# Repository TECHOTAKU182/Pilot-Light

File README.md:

# Pilot Light

一个紧凑型 USB RGB 状态信号灯的开源硬件项目。当前设计版本为 **SL25 Rev B**：通过 CH552G 控制一颗位于正面中心的 WS2812B-V5，使用单个直径 24 mm 的扩散灯窗显示红、黄、绿等状态。

> 本仓库包含可编辑的 PCB、外壳和制造文件，但尚未完成实物打样、光学测试、USB 功能验证或电脑状态采集软件。制造与使用前请自行复核并完成测试。

## 当前设计

| 项目 | SL25 Rev B 规格 |
| --- | --- |
| PCB | 25 x 25 mm、双层、1.6 mm 厚 |
| 光源 | 正面中心 WS2812B-V5 RGB LED |
| 控制器 | CH552G，LED 数据输出为 P1.5 |
| 接口 | 背面 USB-C，USB 2.0 全速原型电路 |
| 外壳 | 30 x 30 x 40 mm |
| 灯窗 | 正面中心直径 24 mm，PET 扩散膜与透明 PC 保护片 |
| 遮光檐 | 顶部前伸 15 mm，两侧连续收短 |

该设计的光学结构从外到内依次为：黑色遮光帽、透明 PC 保护片、PET 扩散膜、泡棉压圈、白色混光腔与中心 RGB LED。白色混光腔是获得较均匀光效的必要零件，不能以黑色打印件替代。

## 仓库结构

| 路径 | 内容 |
| --- | --- |
| [`hardware/sl25_rev_b/`](hardware/sl25_rev_b/) | 当前 Rev B KiCad 工程、BOM、Gerber、贴片坐标、3D 模型与检查报告 |
| [`enclosure/sl25_traffic_rev_b/`](enclosure/sl25_traffic_rev_b/) | 当前 Rev B FreeCAD 工程、STEP、STL、光学片裁切模板与装配说明 |
| [`firmware/ch552_ws2812_demo/`](firmware/ch552_ws2812_demo/) | 用于焊后点灯检查的最小 CH552G 示例程序 |
| [`hardware/reference/`](hardware/reference/) | 器件数据手册和参考图纸 |
| [`SL25-RevB-complete.zip`](SL25-RevB-complete.zip) | Rev B 完整交付包 |
| [`hardware/SL25-RevB-gerbers.zip`](hardware/SL25-RevB-gerbers.zip) | Rev B PCB 制板文件包 |
| [`enclosure/SL25-Traffic-STL-RevB.zip`](enclosure/SL25-Traffic-STL-RevB.zip) | Rev B 3D 打印和膜片裁切文件包 |

`hardware/sl25/` 与 `enclosure/sl25_traffic/` 为历史 Rev A 文件，仅供参考。Rev A 和 Rev B 的 LED、元件安装面、外壳及控制方式不兼容，不能混用。

## 制造与装配

1. 使用 `hardware/SL25-RevB-gerbers.zip` 下单 PCB；建议规格为 FR-4、2 层、1.6 mm、1 oz 铜。
2. 根据 [`hardware/sl25_rev_b/BOM.csv`](hardware/sl25_rev_b/BOM.csv) 和 [`MATERIALS.md`](hardware/sl25_rev_b/MATERIALS.md) 采购并装配；所有元件和 USB-C 均在 PCB 背面，只有 WS2812B-V5 位于正面。
3. 打印 Rev B 的四个外壳件。前壳和遮光帽使用黑色材料，混光腔必须使用不透光白色材料；建议 PETG、0.4 mm 喷嘴、0.16-0.20 mm 层高。
4. 按 `cut_templates/` 中 1:1 SVG 裁切直径 26 mm 的透明 PC 保护片、PET 扩散膜和泡棉环；先测量模板中的 10 x 10 mm 校准框。
5. 参考 [外壳装配说明](enclosure/sl25_traffic_rev_b/README.md) 完成装配。需要两颗 M2 x 12、头径不超过 4.0 mm 的 90 度沉头螺丝。
6. 使用 [`firmware/ch552_ws2812_demo/`](firmware/ch552_ws2812_demo/) 的台架程序确认红、绿、蓝、黄依次点亮，再进行完整功能开发。

完整尺寸、材料规格、打印方向、光学叠层和拆装步骤见 [外壳 README](enclosure/sl25_traffic_rev_b/README.md)。电路、USB/LED 引脚、制造规则和检验结果见 [PCB README](hardware/sl25_rev_b/README.md)。

## 开发与重建

- PCB 使用 KiCad 10。更新设计时，先保留手工修改，再依次运行 `hardware/generate_rev_b.py`、`hardware/route_rev_b.py` 和 `hardware/finish_board.py`；这些生成流程会覆盖已有输出。
- 外壳使用 FreeCAD。修改 `enclosure/sl25_traffic_rev_b/parameters.json` 后，依次运行 `build.py`、`finish_cad.py`、`render.py` 和 `cut_templates.py`。
- 固件使用 SDCC，并需要 WCH CH55X EVT 提供的启动文件。示例程序只用于点灯检查，正式固件应加入 USB 枚举、主机命令超时关灯、USB 挂起关灯和看门狗。

## 验证状态与限制

仓库中的 ERC、DRC、制造文件、模型资产和几何干涉检查已通过，但以下事项尚待实物确认：

- USB 电气性能、枚举和 USB-C 兼容性
- LED 的 WS2812 时序、功耗、温升和各颜色亮度
- 扩散膜下的均匀度、色斑和黄色配比
- 3D 打印公差、膜材厚度、螺丝配合和机械耐久

本项目不是通过认证的交通信号灯，也不应在安全关键或监管用途部署。

## 许可证

尚未指定许可证。在许可证补充前，请先联系仓库所有者确认使用、修改和分发权限。

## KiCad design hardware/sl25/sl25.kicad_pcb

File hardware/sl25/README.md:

# SL25 状态灯 PCB，Rev A

这是一块面向个人原型的 25 × 25 mm 双层 USB 状态灯 PCB，可用于正面宽、高均不超过 30 mm 的外壳。当前完成硬件设计和软件规则检查，尚未制作、焊接或实测。固件、Windows 状态采集程序和外壳工程不包含在本次交付中。

## 打开工程

使用 KiCad 10 打开 `sl25.kicad_pro`，分别进入原理图和 PCB 编辑器。符号、封装和所用 STEP 模型均随工程提供。KiCad 三维查看器可查看装配效果。

| 文件 | 内容 |
| --- | --- |
| `sl25.kicad_sch` | 单页原理图 |
| `sl25.kicad_pcb` | 已布线、铺铜的 PCB |
| `BOM.csv` | 逐项材料表，含准确型号与安装面 |
| `MATERIALS.md` | 中文采购及装配说明 |
| `checks/erc.rpt`、`checks/drc.rpt` | 最终规则检查报告 |
| `fabrication/` | Gerber、独立 PTH/NPTH 钻孔、贴装坐标 |
| `mechanical/sl25.step` | 含元件的装配 STEP，供外壳设计参考 |
| `mechanical/interface.json` | 板框、安装孔和接口位置 |
| `preview/` | 原理图 SVG 及 PCB 正反面、立体预览 |

本文件夹中的材料表替代之前讨论的 Pico 开发板和洞洞板采购方案。USB-C 插座必须匹配指定封装，不能仅凭“16 脚 Type-C”购买替代件。

## 电路

- USB-C 仅使用 USB 2.0 数据与 5 V 供电，CC1、CC2 各自用 5.1 kΩ 电阻接地。没有 USB PD 升压、电池或外部电源接口。
- CH552G 使用 SOP-16 窄体封装、内部振荡器和内部 USB 上拉。VCC 接 USB 5 V；V33 仅接 100 nF 去耦，不能短接到 5 V。
- USBLC6-2SC6 在背面保护 D+、D-；C4 是其电源去耦。插座金属壳直接接 GND，壳体焊脚直接接地铜皮。
- 单颗共阴 RGB 灯的每个阳极分别串 1 kΩ，限流后由 MCU GPIO 驱动。以 5.25 V 和 1% 电阻下限估算，即使忽略 LED 压降，单路电流也不超过 5.31 mA。
- JP1 平时保持断开；通过 10 kΩ 将 D+ 临时拉到 5 V，在上电时请求兼容工厂 USB ISP 的下载模式。购买带工厂 USB ISP 的 CH552G。TP3–TP6 保留专用编程器信号，不能当作通用 SPI 外设接口。
- R7 将高有效 RESET 下拉到 GND。固件仍应采用上电复位和看门狗。

| 功能 | CH552G 物理脚 | GPIO | 备注 |
| --- | --- | --- | --- |
| 红灯 | 3 | P1.5 | PWM1；高电平亮 |
| 绿灯 | 11 | P3.4 | PWM2；高电平亮 |
| 蓝灯 | 9 | P1.1 | 普通 GPIO，默认关闭 |
| USB D+ | 12 | P3.6 | USB 功能 |
| USB D- | 13 | P3.7 | USB 功能 |
| RESET | 6 | RST | 高有效 |

红加绿形成黄色。PWM 占空比需在样板和最终灯罩上调整，不能保证两路相同占空比就得到视觉上均匀的黄色。

## 固件与电脑端约定

建议后续固件使用 USB HID 接收颜色、亮度和灯效命令，Windows 程序通过 HID 库发送，无需增加 USB 转串口芯片。未配置、USB 挂起和主机命令超时应关闭 LED；初始化时先将三路输出置低，再使能输出，红绿用硬件 PWM，蓝色默认不用。

USB VID/PID 和描述符在固件阶段确定，不能未经授权用于发布产品。USB 功耗描述和挂起电流必须与实测匹配。当前电路未验证 USB 枚举、信号质量、EMC 或 ESD 性能；放置保护器件不等于通过系统级认证。

Windows 桌面版 Codex 的实时状态来源仍需单独验证。PCB 本身只接收灯光命令，不会自动读取 Codex。

## 制板与机械

建议首批 5 块样板：双层 FR-4、1.6 mm、1 oz 铜、绿色阻焊、白色丝印；优先选择平整表面处理，USB-C 手焊可选沉金。没有阻抗控制声明。

布线宽度 0.20 mm，设计最小铜间距 0.15 mm；过孔 0.60 / 0.30 mm。安装孔 2.20 mm，LED 孔 0.90 mm；PTH 和 NPTH 分开导出。USB4105 厂家推荐焊盘到定位孔的最近距离约 0.194 mm，本项目孔到铜间距规则设为 0.18 mm；下单时需要工厂支持这一要求。没有通过忽略 DRC 错误来放行设计。

板框圆角半径 1 mm。以 PCB 左上角为平面坐标原点，X 向右、Y 向下：

| 项目 | 位置或尺寸，mm |
| --- | --- |
| PCB 外形 | 25 × 25 × 1.6 |
| H1、H2 安装孔 | (2.7, 2.7)、(22.3, 2.7)，孔径 2.2 |
| D1 光学中心 | (12.5, 3.5)，靠近板上边，不在板中心 |
| USB 插座封装原点 | (12.5, 21.15)，插拔方向朝下边 |
| USB 插座本体 | 厂家宽 8.94、长 7.35、高 3.31 |
| LED 引脚孔 | X=9.2615 / 11.4205 / 13.5795 / 15.7385；Y=3.5 |

建议外壳先按 30 × 30 × 25 mm 预留，厚度尚未与用户锁定。壁厚与装配间隙需在外壳建模时分配，底面需留出 U2、C4 和焊点空间。两个 M2 安装柱配合底部承托或导轨固定 PCB，避免 USB 插拔力只作用在焊脚上。

LED 需用工具夹住靠近封装的一段引脚，再将外侧引脚整形成 2.159 mm 间距，封装底面离板约 3 mm，不要紧贴树脂根部弯折。灯珠顶面及焊接公差在外壳内至少按板上方 12.5 mm 预留，再留混光距离。STEP 中 LED 为通用 KiCad 模型，蓝色外观只是模型材质；实际指定灯珠为透明 RGB。该模型不能替代实物高度和透光测试。

STEP 使用 PCB 左上角 `(100,100)` 作为导出原点；CAD 的 Y 轴可能与上述 PCB 屏幕坐标相反，导入后以安装孔和 USB 方向识别朝向。

## 验证状态

2026-09-05 使用 KiCad 10.0.6：ERC 为 0 错误、0 警告；DRC 为 0 违规、0 未连接、0 原理图一致性问题。检查了厂家引脚图、封装尺寸图和正反面三维预览。

这些是设计文件检查，不能替代打样验证。未执行固件烧录、供电测量、USB 插头正反插、亮度混色、热稳定、休眠恢复及外壳装配测试。USB 数据布线为短距离原型布线，未做阻抗提取或信号完整性仿真。

## 设计依据与库许可

- WCH CH552/CH551 数据手册 V1G，第 3–4、19、31–33、70 页；`../reference/CH552.pdf` 为 WCH 原文的 Adafruit 镜像。厂家入口：https://www.wch-ic.com/downloads/CH552DS1_PDF.html
- Kingbright WP154A4SUREQBFZGC，第 1–2 页：https://www.kingbrightusa.com/images/catalog/spec/WP154A4SUREQBFZGC.pdf
- GCT USB4105 厂家图纸：https://gct.co/files/drawings/usb4105.pdf
- ST USBLC6-2SC6：https://www.st.com/resource/en/datasheet/usblc6-2.pdf
- ch55xduino 工程及 USB ISP 上电方式：https://github.com/DeqingSun/ch55xduino
- 随附封装、STEP 模型来自 KiCad 官方库，适用 KiCad 库许可及其例外：https://www.kicad.org/libraries/license/ 。通用芯片模型只表示封装，并不代表芯片品牌或实物标识。

## 重新生成

已交付文件可以直接在 KiCad 中编辑。只有需要重新生成初始设计时才执行以下脚本；重新生成会覆盖手工改板结果，先保留自己的修改。

在项目根目录运行 KiCad 自带 Python：依次执行 `hardware/generate_board.py`、`hardware/route_board.py`、`hardware/finish_board.py`。默认工具路径是本机的 `E:/Kicard`，其他电脑可调整 `KICAD_FOOTPRINT_DIR`、`KICAD_3DMODEL_DIR`。渲染需要 KiCad 用户缓存目录可写，否则可能只显示裸板。

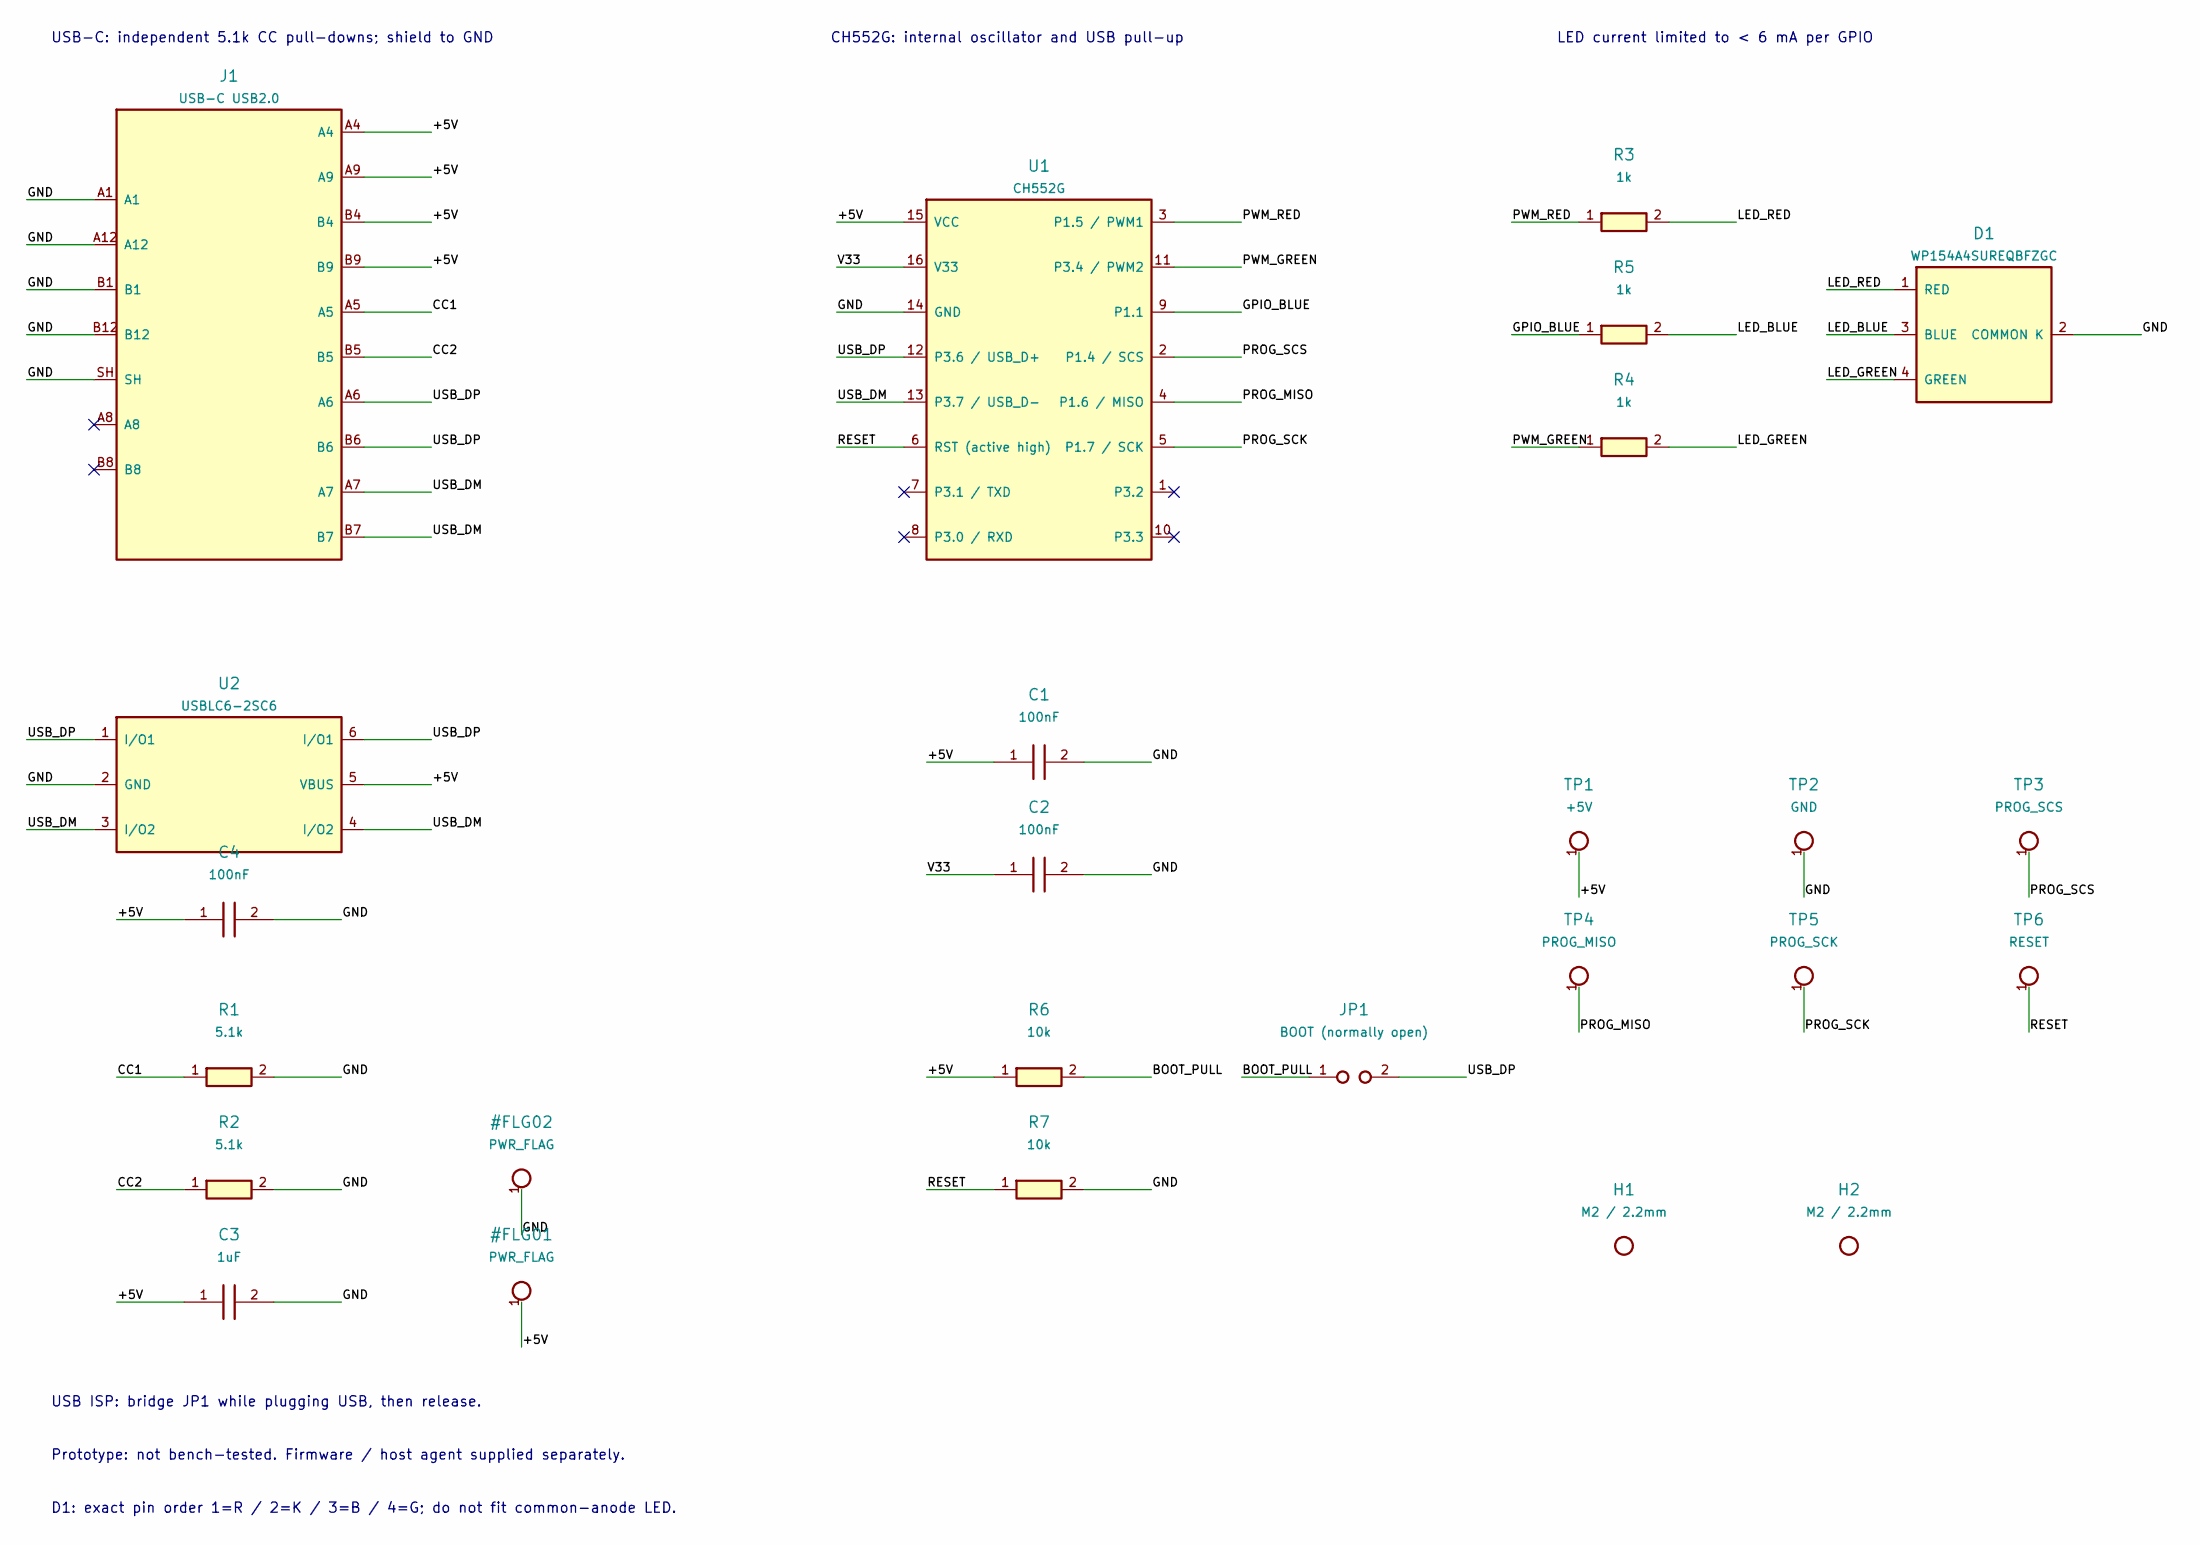
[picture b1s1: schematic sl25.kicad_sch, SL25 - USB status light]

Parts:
C1, C2, C4: 100nF; C_0805_2012Metric
C3: 1uF; C_0805_2012Metric
D1: WP154A4SUREQBFZGC; LED_D5.0mm-4_RGB_Wide_Pins
H1, H2: M2 / 2.2mm; MountingHole_2.2mm_M2
J1: USB-C USB2.0; USB_C_Receptacle_GCT_USB4105-xx-A_16P_TopMnt_Horizontal
JP1: BOOT (normally open); SolderJumper-2_P1.3mm_Open_RoundedPad1.0x1.5mm
R1, R2: 5.1k; R_0805_2012Metric
R3, R4, R5: 1k; R_0805_2012Metric
R6, R7: 10k; R_0805_2012Metric
TP1: +5V; TestPoint_Pad_D1.0mm
TP2: GND; TestPoint_Pad_D1.0mm
TP3: PROG_SCS; TestPoint_Pad_D1.0mm
TP4: PROG_MISO; TestPoint_Pad_D1.0mm
TP5: PROG_SCK; TestPoint_Pad_D1.0mm
TP6: RESET; TestPoint_Pad_D1.0mm
U1: CH552G; SOIC-16_3.9x9.9mm_P1.27mm
U2: USBLC6-2SC6; SOT-23-6

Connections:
/+5V: C1.1, C3.1, C4.1, J1.A4, J1.A9, J1.B4, J1.B9, R6.1, TP1.1, U1.15 (VCC), U2.5 (VBUS)
/BOOT_PULL: JP1.1, R6.2
/CC1: J1.A5, R1.1
/CC2: J1.B5, R2.1
/GND: C1.2, C2.2, C3.2, C4.2, D1.2 (COMMON K), J1.A1, J1.A12, J1.B1, J1.B12, J1.SH, R1.2, R2.2, R7.2, TP2.1, U1.14 (GND), U2.2 (GND)
/GPIO_BLUE: R5.1, U1.9 (P1.1)
/LED_BLUE: D1.3 (BLUE), R5.2
/LED_GREEN: D1.4 (GREEN), R4.2
/LED_RED: D1.1 (RED), R3.2
/PROG_MISO: TP4.1, U1.4 (P1.6 / MISO)
/PROG_SCK: TP5.1, U1.5 (P1.7 / SCK)
/PROG_SCS: TP3.1, U1.2 (P1.4 / SCS)
/PWM_GREEN: R4.1, U1.11 (P3.4 / PWM2)
/PWM_RED: R3.1, U1.3 (P1.5 / PWM1)
/RESET: R7.1, TP6.1, U1.6 (RST (active high))
/USB_DM: J1.A7, J1.B7, U1.13 (P3.7 / USB_D-), U2.3 (I/O2), U2.4 (I/O2)
/USB_DP: J1.A6, J1.B6, JP1.2, U1.12 (P3.6 / USB_D+), U2.1 (I/O1), U2.6 (I/O1)
/V33: C2.1, U1.16 (V33)

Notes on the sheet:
USB-C: independent 5.1k CC pull-downs; shield to GND
CH552G: internal oscillator and USB pull-up
LED current limited to < 6 mA per GPIO
USB ISP: bridge JP1 while plugging USB, then release.
Prototype: not bench-tested. Firmware / host agent supplied separately.
D1: exact pin order 1=R / 2=K / 3=B / 4=G; do not fit common-anode LED.

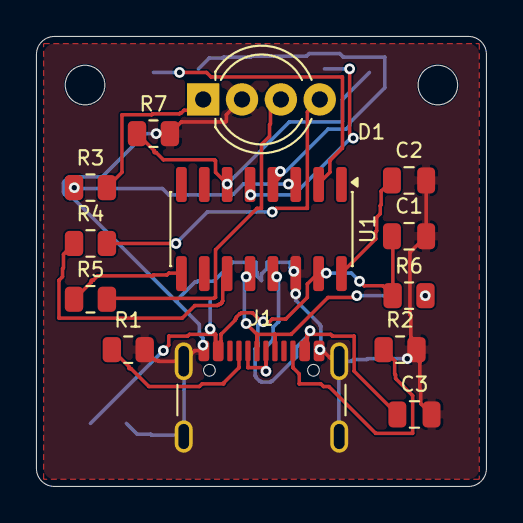
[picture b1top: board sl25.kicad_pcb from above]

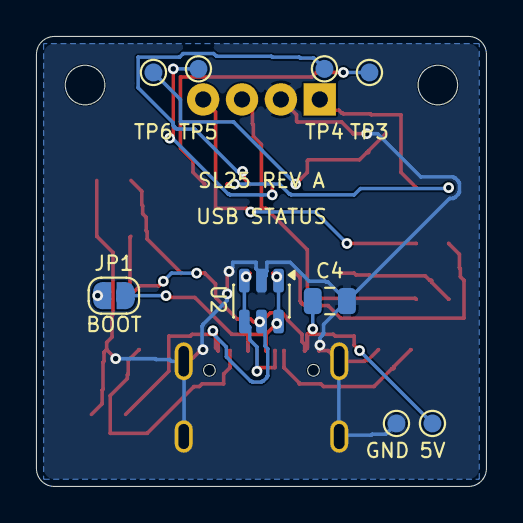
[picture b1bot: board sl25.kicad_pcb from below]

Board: 2 copper layers, 25.0 x 25.0 mm, 24 parts (9 on the bottom side), 18 nets.

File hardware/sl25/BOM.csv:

Reference,Value,MPN_or_specification,Footprint,Side,Quantity,Notes
J1,USB-C USB2.0,GCT USB4105-GF-A,Connector_USB:USB_C_Receptacle_GCT_USB4105-xx-A_16P_TopMnt_Horizontal,Top,1,Exact footprint required; USB-C socket is not interchangeable by appearance.
U1,CH552G,CH552G,Package_SO:SOIC-16_3.9x9.9mm_P1.27mm,Top,1,SOP16 150mil. Buy with factory USB ISP bootloader; do not substitute CH552T/E/P.
U2,USBLC6-2SC6,USBLC6-2SC6,Package_TO_SOT_SMD:SOT-23-6,Bottom,1,Bottom side; pins 1/6 and 3/4 are internally connected line pairs.
D1,WP154A4SUREQBFZGC,WP154A4SUREQBFZGC,LED_THT:LED_D5.0mm-4_RGB_Wide_Pins,Top,1,"Form 1.27mm native leads to 2.159mm PCB pitch with 3mm standoff. 1=R, 2=common K, 3=B, 4=G. Clear lens needs diffuser."
R1,5.1k,0805 5.1k 1% >=0.125W,Resistor_SMD:R_0805_2012Metric,Top,1,
R2,5.1k,0805 5.1k 1% >=0.125W,Resistor_SMD:R_0805_2012Metric,Top,1,
R3,1k,0805 1k 1% >=0.125W,Resistor_SMD:R_0805_2012Metric,Top,1,
R4,1k,0805 1k 1% >=0.125W,Resistor_SMD:R_0805_2012Metric,Top,1,
R5,1k,0805 1k 1% >=0.125W,Resistor_SMD:R_0805_2012Metric,Top,1,
R6,10k,0805 10k 1% >=0.125W,Resistor_SMD:R_0805_2012Metric,Top,1,
R7,10k,0805 10k 1% >=0.125W,Resistor_SMD:R_0805_2012Metric,Top,1,
C1,100nF,0805 100nF X7R 16V,Capacitor_SMD:C_0805_2012Metric,Top,1,
C2,100nF,0805 100nF X7R 16V,Capacitor_SMD:C_0805_2012Metric,Top,1,
C3,1uF,0805 1uF X7R 16V,Capacitor_SMD:C_0805_2012Metric,Top,1,
C4,100nF,0805 100nF X7R 16V,Capacitor_SMD:C_0805_2012Metric,Bottom,1,
JP1,BOOT (normally open),PCB touch pads,Jumper:SolderJumper-2_P1.3mm_Open_RoundedPad1.0x1.5mm,Bottom,1,Momentarily bridge during USB insertion; release after ISP enumeration. Do not solder closed.
TP1,+5V,PCB test pad,TestPoint:TestPoint_Pad_D1.0mm,Bottom,1,Programmer pads use 5V signaling; disconnect USB before external power.
TP2,GND,PCB test pad,TestPoint:TestPoint_Pad_D1.0mm,Bottom,1,Programmer pads use 5V signaling; disconnect USB before external power.
TP3,PROG_SCS,PCB test pad,TestPoint:TestPoint_Pad_D1.0mm,Bottom,1,Programmer pads use 5V signaling; disconnect USB before external power.
TP4,PROG_MISO,PCB test pad,TestPoint:TestPoint_Pad_D1.0mm,Bottom,1,Programmer pads use 5V signaling; disconnect USB before external power.
TP5,PROG_SCK,PCB test pad,TestPoint:TestPoint_Pad_D1.0mm,Bottom,1,Programmer pads use 5V signaling; disconnect USB before external power.
TP6,RESET,PCB test pad,TestPoint:TestPoint_Pad_D1.0mm,Bottom,1,Programmer pads use 5V signaling; disconnect USB before external power.
H1,M2 / 2.2mm,M2 mounting hole,MountingHole:MountingHole_2.2mm_M2,Top,1,
H2,M2 / 2.2mm,M2 mounting hole,MountingHole:MountingHole_2.2mm_M2,Top,1,

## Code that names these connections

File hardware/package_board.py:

"""Check critical hardware invariants and package the already-verified design."""
from pathlib import Path
import hashlib
import json
import math
import zipfile
import pcbnew as pcb

ROOT=Path(__file__).resolve().parent
DESIGN=ROOT/"sl25"
b=pcb.LoadBoard(str(DESIGN/"sl25.kicad_pcb"))
fps={f.GetReference():f for f in b.GetFootprints()}


def net(ref,pin):
    values={p.GetNetname().lstrip('/') for p in fps[ref].Pads() if p.GetNumber()==str(pin)}
    assert len(values)==1,(ref,pin,values)
    return values.pop()


# Pin assignments below are the externally reviewed datasheet expectations.
for pin,expected in {3:"PWM_RED",11:"PWM_GREEN",9:"GPIO_BLUE",12:"USB_DP",13:"USB_DM",14:"GND",15:"+5V",16:"V33"}.items():
    assert net("U1",pin)==expected
for pin,expected in {1:"LED_RED",2:"GND",3:"LED_BLUE",4:"LED_GREEN"}.items():
    assert net("D1",pin)==expected
for pin,expected in {"A6":"USB_DP","B6":"USB_DP","A7":"USB_DM","B7":"USB_DM","A5":"CC1","B5":"CC2","SH":"GND"}.items():
    assert net("J1",pin)==expected
assert net("R1",1)=="CC1" and net("R2",1)=="CC2"
assert net("R1",2)==net("R2",2)=="GND"
assert net("C2",1)=="V33" and net("C2",2)=="GND"
assert net("R6",1)=="+5V" and net("R6",2)==net("JP1",1)=="BOOT_PULL"
assert net("JP1",2)=="USB_DP"
for r in ["R3","R4","R5"]:assert fps[r].GetValue()=="1k"
assert b.GetCopperLayerCount()==2
assert abs(pcb.ToMM(b.GetDesignSettings().GetBoardThickness())-1.6)<.001
for ref,expected in [("H1",(102.7,102.7)),("H2",(122.3,102.7))]:
    assert math.dist(tuple(pcb.ToMM(fps[ref].GetPosition())),expected)<.001
    assert abs(pcb.ToMM(next(iter(fps[ref].Pads())).GetDrillSize().x)-2.2)<.001
for fp in b.GetFootprints():
    for m in fp.Models():
        assert m.m_Filename.startswith("${KIPRJMOD}/models/")
        assert (DESIGN/m.m_Filename.replace("${KIPRJMOD}/","")).is_file()
report=(DESIGN/"checks/drc.rpt").read_text(encoding="utf-8")
for text in ["Found 0 DRC violations","Found 0 unconnected pads","Found 0 Footprint errors"]:assert text in report
erc=(DESIGN/"checks/erc.rpt").read_text(encoding="utf-8")
assert "Errors 0" in erc and "Warnings 0" in erc
step=(DESIGN/"mechanical/sl25.step").read_text(encoding="utf-8")
for expected in ["SOIC-16_3.9x9.9mm_P1.27mm","LED_D5.0mm-4_RGB_Wide_Pins","USB_C_Receptacle_GCT_USB4105","SOT-23-6"]:assert expected in step
for file in ["sl25-PTH.drl","sl25-NPTH.drl","sl25-F_Cu.gtl","sl25-B_Cu.gbl","sl25-Edge_Cuts.gm1"]:
    assert (DESIGN/"fabrication"/file).stat().st_size>100

result={"tool":"KiCad 10.0.6","revision":"A","status":"design_checks_passed_not_bench_tested",
        "footprints":len(fps),"copper_layers":2,"board_mm":[25,25,1.6],
        "erc_errors":0,"erc_warnings":0,"drc_violations":0,"unconnected_pads":0,"schematic_parity_issues":0,
        "critical_pinmap_checks":"passed","local_model_paths":"passed","step_contains_component_models":"passed",
        "physical_validation":"not performed"}
(DESIGN/"checks/verification.json").write_text(json.dumps(result,indent=2),encoding="utf-8")

files=[p for p in DESIGN.rglob("*") if p.is_file() and not p.name.endswith((".lck",".kicad_prl"))]
hashes={str(p.relative_to(DESIGN)).replace("\\","/"):hashlib.sha256(p.read_bytes()).hexdigest()
        for p in files if p.name!="SHA256SUMS.json"}
(DESIGN/"SHA256SUMS.json").write_text(json.dumps(hashes,indent=2),encoding="utf-8")
with zipfile.ZipFile(ROOT/"SL25-RevA-project.zip","w",zipfile.ZIP_DEFLATED) as z:
    for p in DESIGN.rglob("*"):
        if p.is_file() and not p.name.endswith((".lck",".kicad_prl")):
            z.write(p,"SL25-RevA/hardware/sl25/"+str(p.relative_to(DESIGN)))
    for p in ROOT.glob("*.py"):z.write(p,"SL25-RevA/hardware/"+p.name)
    for p in (ROOT/"reference").glob("*.pdf"):z.write(p,"SL25-RevA/hardware/reference/"+p.name)
with zipfile.ZipFile(ROOT/"SL25-RevA-gerbers.zip","w",zipfile.ZIP_DEFLATED) as z:
    for p in (DESIGN/"fabrication").iterdir():
        if p.suffix in [".gtl",".gbl",".gts",".gbs",".gto",".gbo",".gtp",".gbp",".gm1",".drl",".gbrjob"]:z.write(p,p.name)
for name in ["SL25-RevA-project.zip","SL25-RevA-gerbers.zip"]:
    with zipfile.ZipFile(ROOT/name) as z:assert z.testzip() is None
print(json.dumps(result,indent=2))
print("Packages:",ROOT/"SL25-RevA-project.zip",ROOT/"SL25-RevA-gerbers.zip")

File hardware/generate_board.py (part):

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part("U1","CH552G","CH552G","Package_SO:SOIC-16_3.9x9.9mm_P1.27mm",
     (112.5,110.7),(134.62,58.42),
     {15:"+5V",16:"V33",14:"GND",12:"USB_DP",13:"USB_DM",6:"RESET",7:None,8:None,
      3:"PWM_RED",11:"PWM_GREEN",9:"GPIO_BLUE",2:"PROG_SCS",4:"PROG_MISO",5:"PROG_SCK",1:None,10:None},
     angle=270,note="SOP16 150mil. Buy with factory USB ISP bootloader; do not substitute CH552T/E/P.")
part("U2","USBLC6","USBLC6-2SC6","Package_TO_SOT_SMD:SOT-23-6",
     (112.5,114.7),(43.18,104.14),{1:"USB_DP",6:"USB_DP",3:"USB_DM",4:"USB_DM",2:"GND",5:"+5V"},
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    ("R2","5.1k",(120.2,117.4),(43.18,149.86),{1:"CC2",2:"GND"}),
    ("R3","1k",(103.0,108.4),(200.66,40.64),{1:"PWM_RED",2:"LED_RED"}),
    ("R4","1k",(103.0,111.5),(200.66,66.04),{1:"PWM_GREEN",2:"LED_GREEN"}),
    ("R5","1k",(103.0,114.6),(200.66,53.34),{1:"GPIO_BLUE",2:"LED_BLUE"}),
    ("R6","10k",(120.7,114.4),(134.62,137.16),{1:"+5V",2:"BOOT_PULL"}),
    ("R7","10k",(106.5,105.4),(134.62,149.86),{1:"RESET",2:"GND"}),
]:
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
